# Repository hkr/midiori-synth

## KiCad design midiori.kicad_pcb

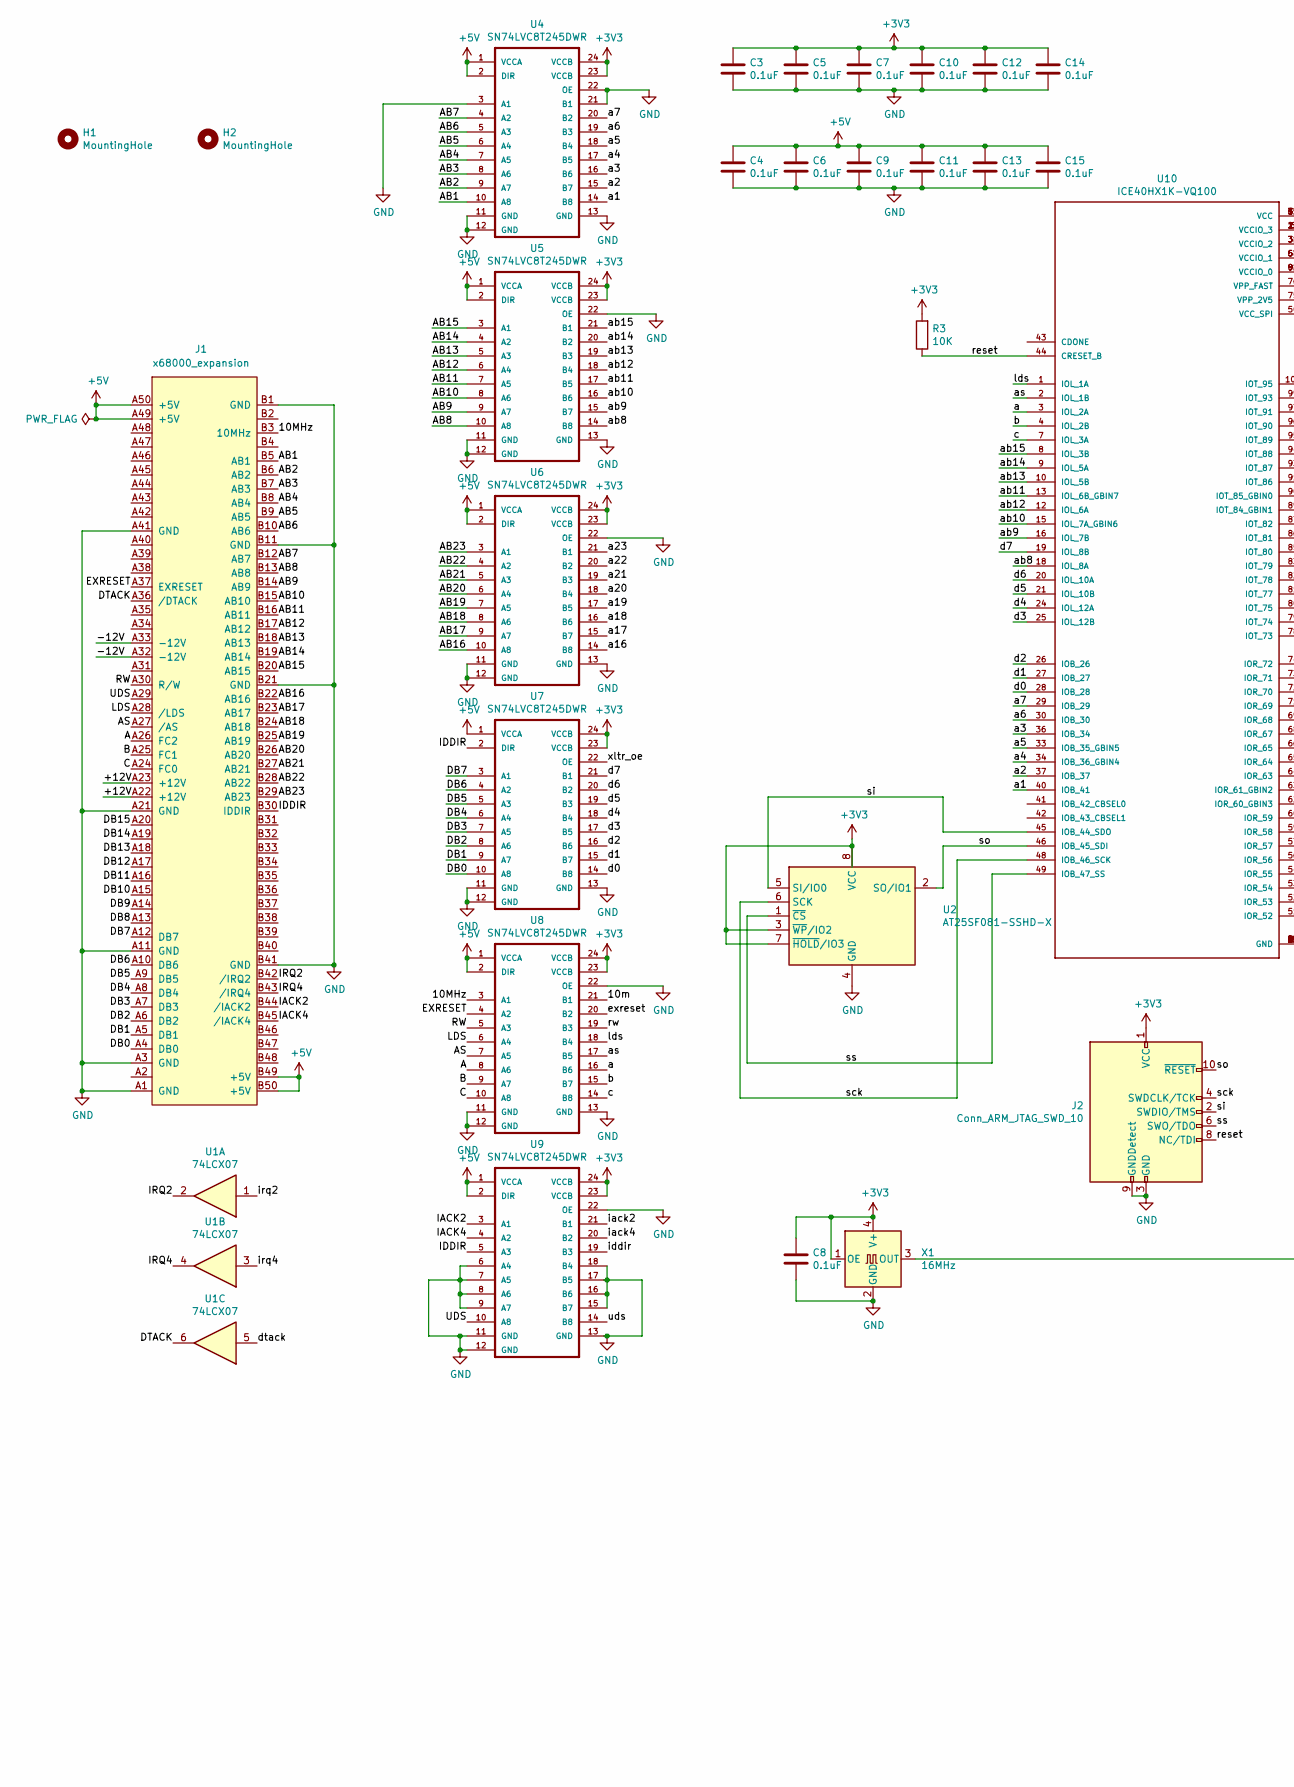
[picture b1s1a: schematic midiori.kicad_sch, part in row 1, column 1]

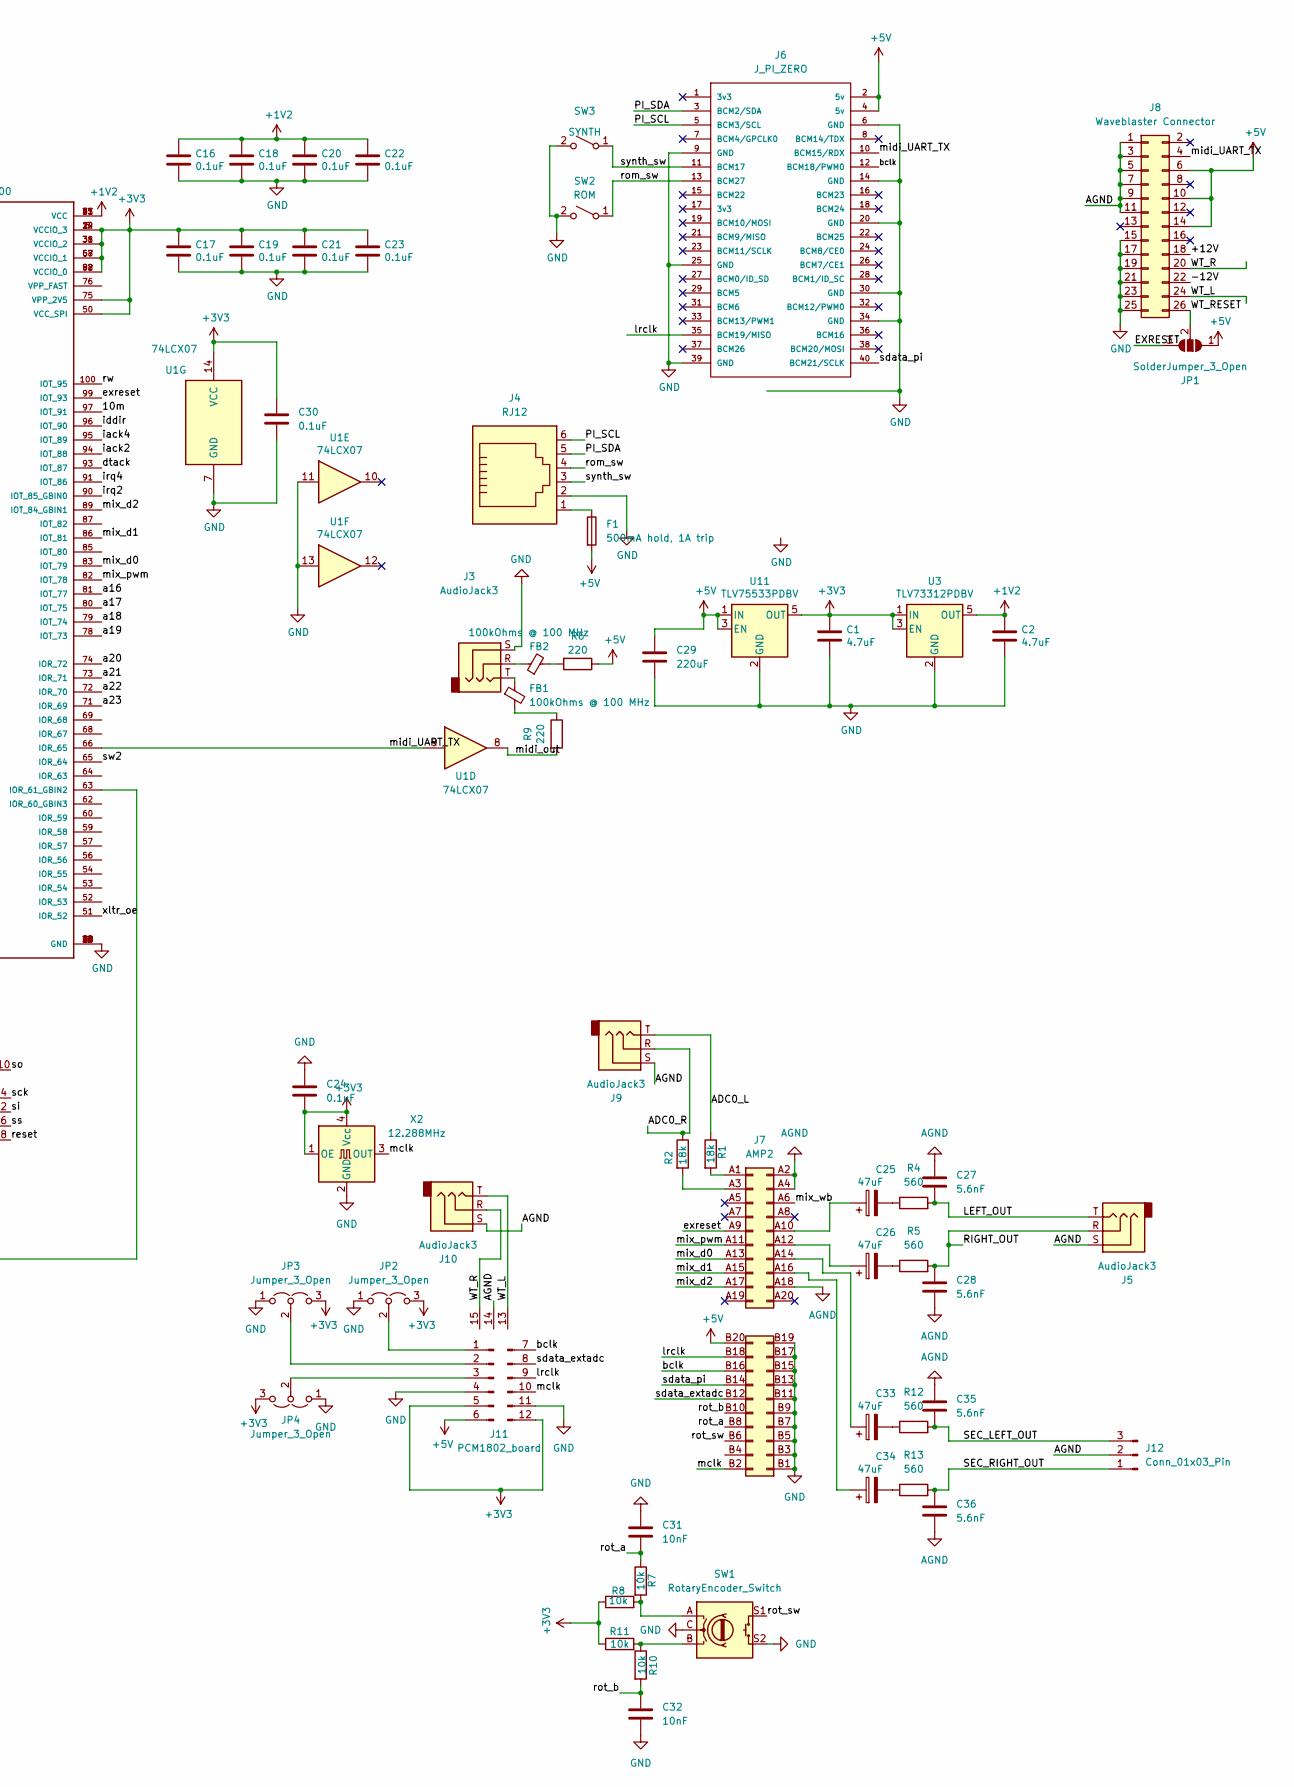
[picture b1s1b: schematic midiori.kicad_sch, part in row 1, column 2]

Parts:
C1, C2: 4.7uF; C_0805_2012Metric
C3, C4, C5, C6, C7, C9, C10, C11, C12, C13, C14, C15, C16, C17, C18, C19, C20, C21, C22, C23, C24, C30: 0.1uF; C_0805_2012Metric
C8: 0.1uF; C_0805_2012Metric_Pad1.15x1.40mm_HandSolder
C25, C26, C33, C34: 47uF; C_Elec_6.3x5.8
C27, C28, C35, C36: 5.6nF; C_0805_2012Metric
C29: 220uF; CP_Radial_D8.0mm_P3.50mm
C31, C32: 10nF; C_0805_2012Metric
F1: 500mA hold, 1A trip; Fuse_1206_3216Metric_Pad1.42x1.75mm_HandSolder
FB1, FB2: 100kOhms @ 100 MHz; L_0805_2012Metric_Pad1.05x1.20mm_HandSolder
H1, H2: MountingHole; MountingHole_3.2mm_M3_Pad
J1: x68000_expansion
J2: Conn_ARM_JTAG_SWD_10; PinHeader_2x05_P1.27mm_Vertical_SMD
J3, J5, J9, J10: AudioJack3; Jack_3.5mm_CUI_SJ1-3535NG_Horizontal
J4: RJ12; RJ12_Amphenol_54601-x06_Horizontal
J6: J_PI_ZERO; RASPBERRYPIZEROWV13
J7: AMP2; AMP2_TH
J8: Waveblaster Connector; PinHeader_2x13_P2.54mm_Vertical
J11: PCM1802_board; PCM1808_board
J12: Conn_01x03_Pin; PinHeader_1x03_P2.54mm_Horizontal
JP1: SolderJumper_3_Open; SolderJumper-3_P1.3mm_Open_Pad1.0x1.5mm
JP2, JP3, JP4: Jumper_3_Open; SolderJumper-3_P1.3mm_Open_RoundedPad1.0x1.5mm
R1, R2: 18k; R_0805_2012Metric
R3: 10K; R_0805_2012Metric
R4, R5, R12, R13: 560; R_0805_2012Metric
R6, R9: 220; R_0805_2012Metric_Pad1.15x1.40mm_HandSolder
R7, R8, R10, R11: 10k; R_0805_2012Metric
SW1: RotaryEncoder_Switch; RotaryEncoder_Bourns_Horizontal_PEC09-2xxxF-Sxxxx
SW2: ROM; SW_Tactile_SPST_Angled_PTS645Vx58-2LFS
SW3: SYNTH; SW_Tactile_SPST_Angled_PTS645Vx58-2LFS
U1: 74LCX07; SOIC-14_3.9x8.7mm_P1.27mm
U2: AT25SF081-SSHD-X; SOIC-8_3.9x4.9mm_P1.27mm
U3: TLV73312PDBV; SOT-23-5
U4, U5, U6, U7, U8, U9: SN74LVC8T245DWR; SOIC-24W_7.5x15.4mm_P1.27mm
U10: ICE40HX1K-VQ100; QFP50P1600X1600X120-100N
U11: TLV75533PDBV; SOT-23-5
X1: 16MHz; Oscillator_SMD_SeikoEpson_SG8002CA-4Pin_7.0x5.0mm
X2: 12.288MHz; Oscillator_SMD_SeikoEpson_SG8002CA-4Pin_7.0x5.0mm

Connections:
+1V2: C2.1, C16.1, C18.1, C20.1, C22.1, U3.5 (OUT), U10.11 (VCC), U10.35 (VCC), U10.61 (VCC), U10.77 (VCC)
+3V3: C1.1, C3.1, C5.1, C7.1, C8.1, C10.1, C12.1, C14.1, C17.1, C19.1, C21.1, C23.1, C24.2, C30.1, J2.1 (VCC), J11.5 (3V3), J11.12 (3V3), JP2.3 (B), JP3.3 (B), JP4.3 (B), R3.2, R8.1, R11.1, U1.14 (VCC), U2.3 (~WP/IO2), U2.7 (~HOLD/IO3), U2.8 (VCC), U3.1 (IN), U3.3 (EN), U4.23 (VCCB), U4.24 (VCCB), U5.23 (VCCB), U5.24 (VCCB), U6.23 (VCCB), U6.24 (VCCB), U7.23 (VCCB), U7.24 (VCCB), U8.23 (VCCB), U8.24 (VCCB), U9.23 (VCCB), U9.24 (VCCB), U10.6 (VCCIO_3), U10.14 (VCCIO_3), U10.22 (VCCIO_3), U10.31 (VCCIO_2), U10.38 (VCCIO_2), U10.50 (VCC_SPI), U10.58 (VCCIO_1), U10.67 (VCCIO_1), U10.75 (VPP_2V5), U10.88 (VCCIO_0), U10.92 (VCCIO_0), U11.5 (OUT), X1.1 (OE), X1.4 (V+), X2.1 (OE), X2.4 (Vcc)
+5V: C4.1, C6.1, C9.1, C11.1, C13.1, C15.1, C29.1, F1.2, J1.A49 (+5V), J1.A50 (+5V), J1.B49 (+5V), J1.B50 (+5V), J6.2 (5v), J6.4 (5v), J7.B20 (VIN), J8.6, J8.10, J8.14, J11.6 (5V), JP1.1 (A), R6.1, U4.1 (VCCA), U4.2 (DIR), U5.1 (VCCA), U5.2 (DIR), U6.1 (VCCA), U6.2 (DIR), U7.1 (VCCA), U8.1 (VCCA), U8.2 (DIR), U9.1 (VCCA), U9.2 (DIR), U11.1 (IN), U11.3 (EN)
/10MHz: J1.B3 (10MHz), U8.3 (A1)
/10m: U8.21 (B1), U10.97 (IOT_91)
/+12V: J1.A22 (+12V), J1.A23 (+12V), J8.18
/-12V: J1.A32 (-12V), J1.A33 (-12V), J8.22
/A: J1.A26 (FC2), U8.8 (A6)
/AB1: J1.B5 (AB1), U4.10 (A8)
/AB2: J1.B6 (AB2), U4.9 (A7)
/AB3: J1.B7 (AB3), U4.8 (A6)
/AB4: J1.B8 (AB4), U4.7 (A5)
/AB5: J1.B9 (AB5), U4.6 (A4)
/AB6: J1.B10 (AB6), U4.5 (A3)
/AB7: J1.B12 (AB7), U4.4 (A2)
/AB8: J1.B13 (AB8), U5.10 (A8)
/AB9: J1.B14 (AB9), U5.9 (A7)
/AB10: J1.B15 (AB10), U5.8 (A6)
/AB11: J1.B16 (AB11), U5.7 (A5)
/AB12: J1.B17 (AB12), U5.6 (A4)
/AB13: J1.B18 (AB13), U5.5 (A3)
/AB14: J1.B19 (AB14), U5.4 (A2)
/AB15: J1.B20 (AB15), U5.3 (A1)
/AB16: J1.B22 (AB16), U6.10 (A8)
/AB17: J1.B23 (AB17), U6.9 (A7)
/AB18: J1.B24 (AB18), U6.8 (A6)
/AB19: J1.B25 (AB19), U6.7 (A5)
/AB20: J1.B26 (AB20), U6.6 (A4)
/AB21: J1.B27 (AB21), U6.5 (A3)
/AB22: J1.B28 (AB22), U6.4 (A2)
/AB23: J1.B29 (AB23), U6.3 (A1)
/ADC0_L: J9.T, R1.1
/ADC0_R: J9.R, R2.1
/AS: J1.A27 (/AS), U8.7 (A5)
/B: J1.A25 (FC1), U8.9 (A7)
/C: J1.A24 (FC0), U8.10 (A8)
/DB0: J1.A4 (DB0), U7.10 (A8)
/DB1: J1.A5 (DB1), U7.9 (A7)
/DB2: J1.A6 (DB2), U7.8 (A6)
/DB3: J1.A7 (DB3), U7.7 (A5)
/DB4: J1.A8 (DB4), U7.6 (A4)
/DB5: J1.A9 (DB5), U7.5 (A3)
/DB6: J1.A10 (DB6), U7.4 (A2)
/DB7: J1.A12 (DB7), U7.3 (A1)
/DB8: J1.A13
/DB9: J1.A14
/DB10: J1.A15
/DB11: J1.A16
/DB12: J1.A17
/DB13: J1.A18
/DB14: J1.A19
/DB15: J1.A20
/DTACK: J1.A36 (/DTACK), U1.6
/EXRESET: J1.A37 (EXRESET), JP1.3 (B), U8.4 (A2)
/IACK2: J1.B44 (/IACK2), U9.3 (A1)
/IACK4: J1.B45 (/IACK4), U9.4 (A2)
/IDDIR: J1.B30 (IDDIR), U7.2 (DIR), U9.5 (A3)
/IRQ2: J1.B42 (/IRQ2), U1.2
/IRQ4: J1.B43 (/IRQ4), U1.4
/LDS: J1.A28 (/LDS), U8.6 (A4)
/LEFT_OUT: C27.2, J5.T, R4.2
/PI_SCL: J4.6, J6.5 (BCM3/SCL)
/PI_SDA: J4.5, J6.3 (BCM2/SDA)
/RIGHT_OUT: C28.1, J5.R, R5.2
/RW: J1.A30 (R/W), U8.5 (A3)
/SEC_LEFT_OUT: C35.2, J12.3, R12.2
/SEC_RIGHT_OUT: C36.1, J12.1, R13.2
/UDS: J1.A29, U9.10 (A8)
/WT_L: J8.24, J10.T, J11.13 (LIN)
/WT_R: J8.20, J10.R, J11.15 (RIN)
/WT_RESET: J8.26, JP1.2 (C)
/a: U8.16 (B6), U10.3 (IOL_2A)
/a1: U4.14 (B8), U10.40 (IOB_41)
/a2: U4.15 (B7), U10.37 (IOB_37)
/a3: U4.16 (B6), U10.36 (IOB_34)
/a4: U4.17 (B5), U10.34 (IOB_36_GBIN4)
/a5: U4.18 (B4), U10.33 (IOB_35_GBIN5)
/a6: U4.19 (B3), U10.30 (IOB_30)
/a7: U4.20 (B2), U10.29 (IOB_29)
/a16: U6.14 (B8), U10.81 (IOT_77)
/a17: U6.15 (B7), U10.80 (IOT_75)
/a18: U6.16 (B6), U10.79 (IOT_74)
/a19: U6.17 (B5), U10.78 (IOT_73)
/a20: U6.18 (B4), U10.74 (IOR_72)
/a21: U6.19 (B3), U10.73 (IOR_71)
/a22: U6.20 (B2), U10.72 (IOR_70)
/a23: U6.21 (B1), U10.71 (IOR_69)
/ab8: U5.14 (B8), U10.18 (IOL_8A)
/ab9: U5.15 (B7), U10.16 (IOL_7B)
/ab10: U5.16 (B6), U10.15 (IOL_7A_GBIN6)
/ab11: U5.17 (B5), U10.13 (IOL_6B_GBIN7)
/ab12: U5.18 (B4), U10.12 (IOL_6A)
/ab13: U5.19 (B3), U10.10 (IOL_5B)
/ab14: U5.20 (B2), U10.9 (IOL_5A)
/ab15: U5.21 (B1), U10.8 (IOL_3B)
/as: U8.17 (B5), U10.2 (IOL_1B)
/b: U8.15 (B7), U10.4 (IOL_2B)
/bclk: J6.12 (BCM18/PWM0), J7.B16 (MP5), J11.7 (BCK)
/c: U8.14 (B8), U10.7 (IOL_3A)
/d0: U7.14 (B8), U10.28 (IOB_28)
/d1: U7.15 (B7), U10.27 (IOB_27)
/d2: U7.16 (B6), U10.26 (IOB_26)
/d3: U7.17 (B5), U10.25 (IOL_12B)
/d4: U7.18 (B4), U10.24 (IOL_12A)
/d5: U7.19 (B3), U10.21 (IOL_10B)
/d6: U7.20 (B2), U10.20 (IOL_10A)
/d7: U7.21 (B1), U10.19 (IOL_8B)
/dtack: U1.5, U10.93 (IOT_87)
/exreset: J7.A9 (/RESET), U8.20 (B2), U10.99 (IOT_93)
/iack2: U9.21 (B1), U10.94 (IOT_88)
/iack4: U9.20 (B2), U10.95 (IOT_89)
/iddir: U9.19 (B3), U10.96 (IOT_90)
/irq2: U1.1, U10.90 (IOT_85_GBIN0)
/irq4: U1.3, U10.91 (IOT_86)
/lds: U8.18 (B4), U10.1 (IOL_1A)
/lrclk: J6.35 (BCM19/MISO), J7.B18 (MP4), J11.9 (LRC)
/mclk: J7.B2 (MCLK), J11.10 (SCK), X2.3 (OUT)
/midi_UART_TX: J6.10 (BCM15/RDX), J8.4, U1.9, U10.66 (IOR_65)
/midi_out: R9.2, U1.8
/mix_d0: J7.A13 (MP3), U10.83 (IOT_79)
/mix_d1: J7.A15 (MP8), U10.86 (IOT_81)
/mix_d2: J7.A17 (MP9), U10.89 (IOT_84_GBIN1)
/mix_pwm: J7.A11 (MP2), U10.82 (IOT_78)
/mix_wb: J7.A6 (WB)
/reset: J2.8 (NC/TDI), R3.1, U10.44 (CRESET_B)
/rom_sw: J4.4, J6.13 (BCM27), SW2.1 (A)
/rot_a: C31.2, J7.B8 (MP6), R7.1
/rot_b: C32.2, J7.B10 (MP7), R10.2
/rot_sw: J7.B6 (MP10), SW1.S1
/rw: U8.19 (B3), U10.100 (IOT_95)
/sck: J2.4 (SWDCLK/TCK), U2.6 (SCK), U10.48 (IOB_46_SCK)
/sdata_extadc: J7.B12 (MP0), J11.8 (OUT)
/sdata_pi: J6.40 (BCM21/SCLK), J7.B14 (MP1)
/si: J2.2 (SWDIO/TMS), U2.5 (SI/IO0), U10.45 (IOB_44_SDO)
/so: J2.10 (~RESET), U2.2 (SO/IO1), U10.46 (IOB_45_SDI)
/ss: J2.6 (SWO/TDO), U2.1 (~CS), U10.49 (IOB_47_SS)
/sw2: U10.65 (IOR_64)
/synth_sw: J4.3, J6.11 (BCM17), SW3.1 (A)
/uds: U9.14 (B8)
/xltr_oe: U7.22 (OE), U10.51 (IOR_52)
AGND: C27.1, C28.2, C35.1, C36.2, J5.S, J7.A2 (GND), J7.A4 (GND), J7.A18 (GND), J8.1, J8.3, J8.5, J8.7, J8.9, J8.11, J9.S, J10.S, J11.14 (GND), J12.2
GND: C1.2, C2.2, C3.2, C4.2, C5.2, C6.2, C7.2, C8.2, C9.2, C10.2, C11.2, C12.2, C13.2, C14.2, C15.2, C16.2, C17.2, C18.2, C19.2, C20.2, C21.2, C22.2, C23.2, C24.1, C29.2, C30.2, C31.1, C32.1, J1.A1 (GND), J1.A3 (GND), J1.A11 (GND), J1.A21 (GND), J1.A41 (GND), J1.B1 (GND), J1.B11 (GND), J1.B21 (GND), J1.B41 (GND), J2.3 (GND), J2.5 (GND), J2.9 (GNDDetect), J3.S, J4.2, J6.6 (GND), J6.9 (GND), J6.14 (GND), J6.20 (GND), J6.25 (GND), J6.30 (GND), J6.34 (GND), J6.39 (GND), J7.B1 (GND), J7.B3 (GND), J7.B5 (GND), J7.B7 (GND), J7.B9 (GND), J7.B11 (GND), J7.B13 (GND), J7.B15 (GND), J7.B17 (GND), J7.B19 (GND), J8.15, J8.17, J8.19, J8.21, J8.23, J8.25, J11.4 (GND), J11.11 (GND), JP2.1 (A), JP3.1 (A), JP4.1 (A), SW1.C, SW1.S2, SW2.2 (B), SW3.2 (B), U1.7 (GND), U1.11, U1.13, U2.4 (GND), U3.2 (GND), U4.3 (A1), U4.11 (GND), U4.12 (GND), U4.13 (GND), U4.21 (B1), U4.22 (OE), U5.11 (GND), U5.12 (GND), U5.13 (GND), U5.22 (OE), U6.11 (GND), U6.12 (GND), U6.13 (GND), U6.22 (OE), U7.11 (GND), U7.12 (GND), U7.13 (GND), U8.11 (GND), U8.12 (GND), U8.13 (GND), U8.22 (OE), U9.6 (A4), U9.7 (A5), U9.8 (A6), U9.9 (A7), U9.11 (GND), U9.12 (GND), U9.13 (GND), U9.15 (B7), U9.16 (B6), U9.17 (B5), U9.18 (B4), U9.22 (OE), U10.5 (GND), U10.17 (GND), U10.23 (GND), U10.32 (GND), U10.39 (GND), U10.47 (GND), U10.55 (GND), U10.70 (GND), U10.84 (GND), U10.98 (GND), U11.2 (GND), X1.2 (GND), X2.2 (GND)
unnamed: C25.2, R4.1
unnamed: C26.2, R5.1
unnamed: C33.2, R12.1
unnamed: C34.2, R13.1
unnamed: F1.1, J4.1
unnamed: FB1.1, J3.T
unnamed: FB1.2, R9.1
unnamed: FB2.1, J3.R
unnamed: FB2.2, R6.2
unnamed: J7.A1 (AD0), R1.2
unnamed: J7.A3 (AD1), R2.2
unnamed: C25.1, J7.A10 (DAC0)
unnamed: C26.1, J7.A12 (DAC1)
unnamed: C33.1, J7.A14 (DAC2)
unnamed: C34.1, J7.A16 (DAC3)
unnamed: J11.3 (MD0), JP4.2 (C)
unnamed: J11.2 (MD1), JP3.2 (C)
unnamed: J11.1, JP2.2 (C)
unnamed: R7.2, R8.2, SW1.A
unnamed: R10.1, R11.2, SW1.B
unnamed: U10.63 (IOR_61_GBIN2), X1.3 (OUT)

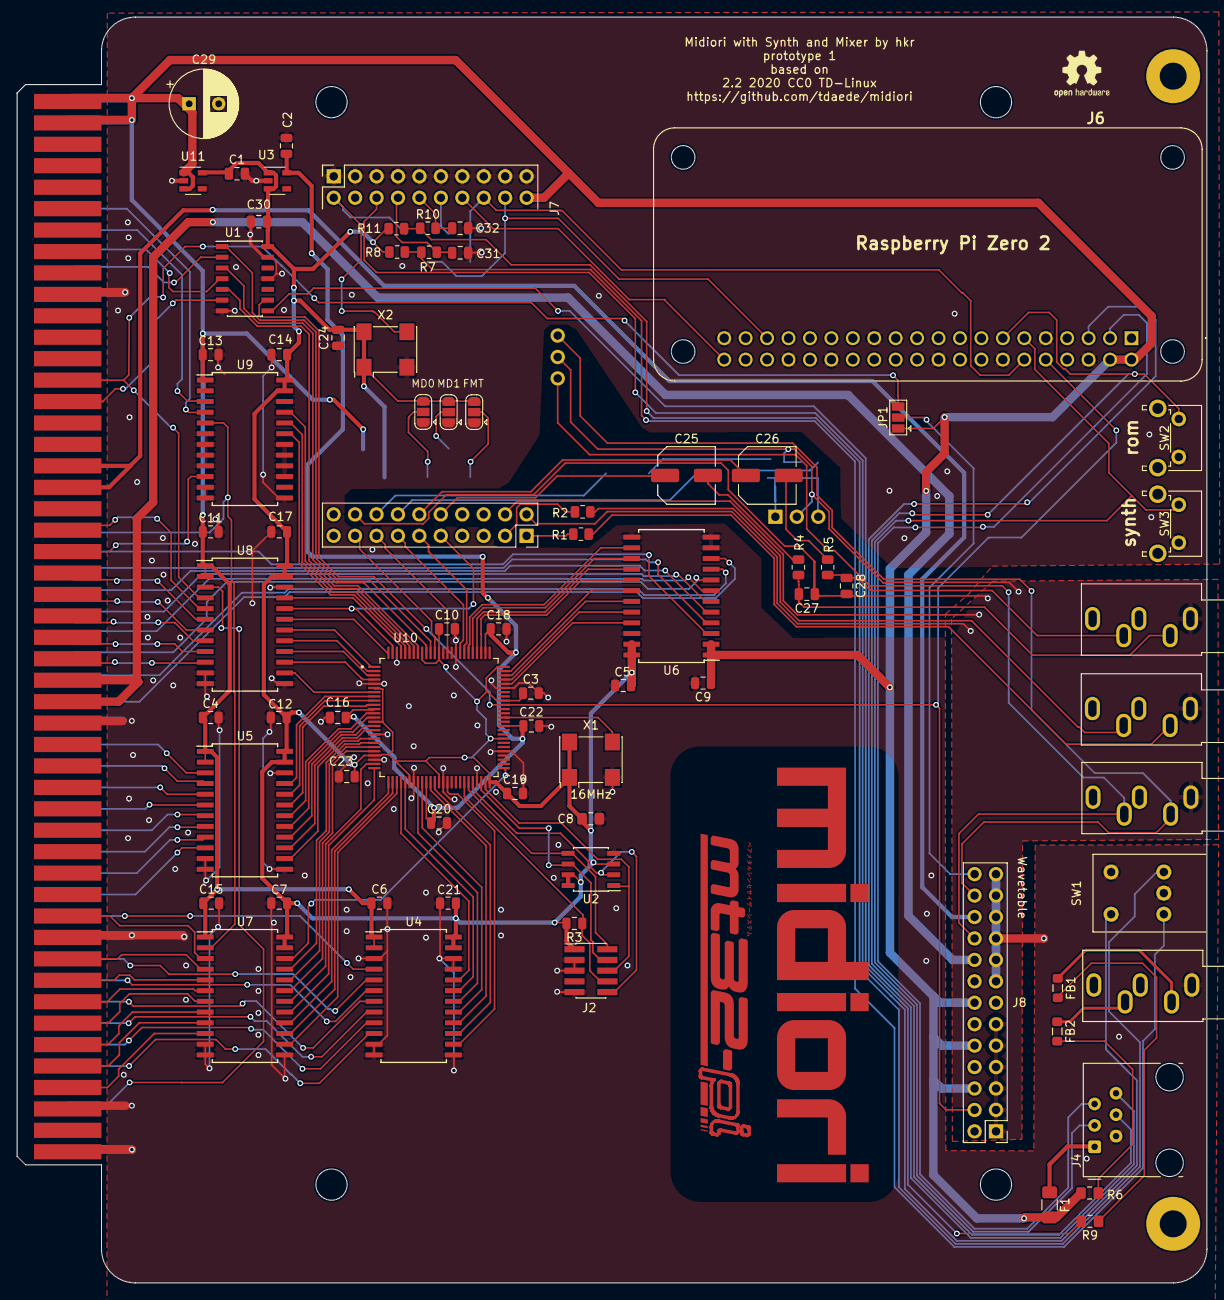
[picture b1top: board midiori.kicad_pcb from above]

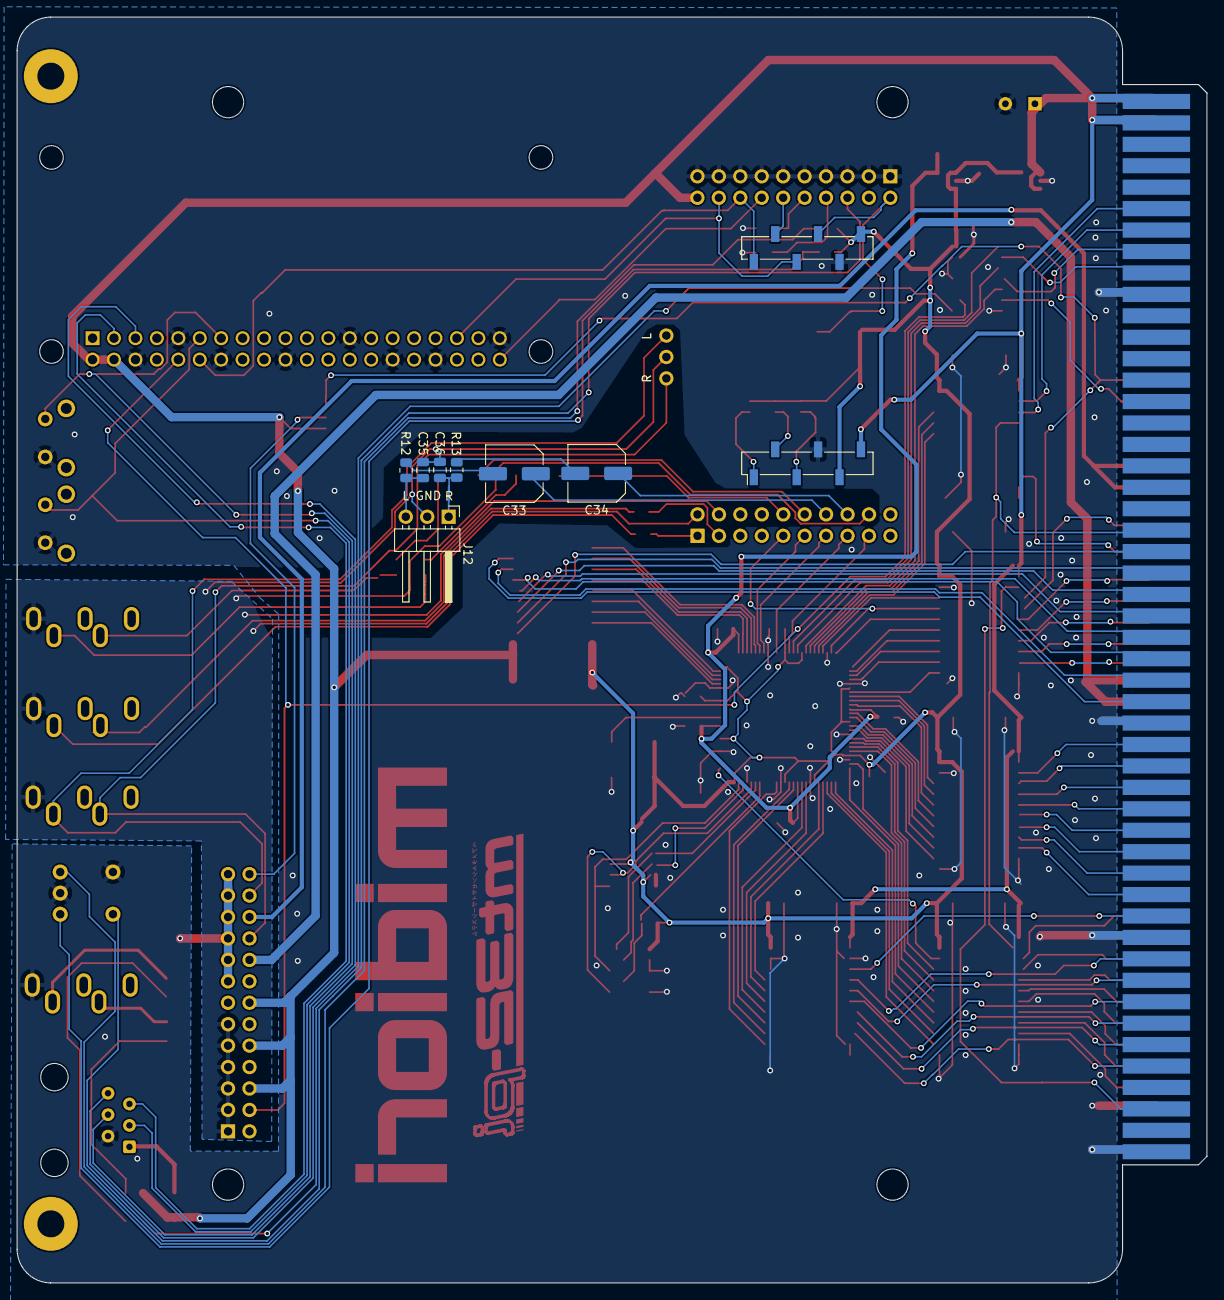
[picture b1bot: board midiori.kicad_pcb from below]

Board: 2 copper layers, 141.0 x 150.0 mm, 87 parts (8 on the bottom side), 152 nets.

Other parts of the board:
svg2mod: G***; midiori_logo

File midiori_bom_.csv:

Component,Description,Part,References,Value,Footprint,Quantity Per PCB,Datasheet,Field4,Field5,Field6,Field7,Field8
1,Unpolarized capacitor,C,C3 C4 C5 C6 C7 C9 C10 C11 C12 C13 C14 C15 C16 C17 C18 C19 C20 C21 C22 C23 C28 C30,0.1uF,C_0805_2012Metric,22,~,,,,,
2,Unpolarized capacitor,C,C8,0.1uF,C_0805_2012Metric_Pad1.15x1.40mm_HandSolder,1,~,,,,,
3,Unpolarized capacitor,C,C1 C2,4.7uF,C_0805_2012Metric,2,~,,,,,
4,Unpolarized capacitor,C,C29,220uF,CP_Radial_D8.0mm_P3.50mm,1,~,,,,,
5,Fuse,Fuse,F1,"500mA hold, 1A trip",Fuse_1206_3216Metric_Pad1.42x1.75mm_HandSolder,1,~,,,,,
6,"Ferrite bead, small symbol",FerriteBead_Small,FB1 FB2,100kOhms @ 100 MHz,L_0805_2012Metric_Pad1.05x1.20mm_HandSolder,2,~,,,,,
7,"Audio Jack, 3 Poles (Stereo / TRS)",AudioJack3,J3,AudioJack3,Jack_3.5mm_CUI_SJ1-3535NG_Horizontal,1,~,,,,,
8,"Audio Jack, 3 Poles (Stereo / TRS)",AudioJack3,J5 J9,AudioJack3,Jack_3.5mm_CUI_SJ1-3535NG_Horizontal,2,~,,,,,
9,,Conn_ARM_JTAG_SWD_10-Connector-midiori-rescue-midiori-rescue,J2,Conn_ARM_JTAG_SWD_10,PinHeader_2x05_P1.27mm_Vertical_SMD,1,http://infocenter.arm.com/help/topic/com.arm.doc.faqs/attach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,,,,,
10,,J_PI_ZERO,J6,J_PI_ZERO,RASPBERRYPIZEROWV13,1,,,,,,
11,"RJ connector, 6P6C (6 positions 6 connected)",RJ12,J4,RJ12,RJ12_Amphenol_54601-x06_Horizontal,1,~,,,,,
12,"Generic connector, double row, 02x13, odd/even pin numbering scheme (row 1 odd numbers, row 2 even numbers), script generated (kicad-library-utils/schlib/autogen/connector/)",Conn_02x13_Odd_Even,J8,Waveblaster Connector,PinHeader_2x13_P2.54mm_Vertical,1,~,,,,,
13,,x68000_expansion-x68k-midiori-rescue-midiori-rescue,J1,x68000_expansion,x68000_expansion,1,,,,,,
14,"Solder Jumper, 3-pole, open",SolderJumper_3_Open,JP1,SolderJumper_3_Open,SolderJumper-3_P1.3mm_Open_Pad1.0x1.5mm,1,~,,,,,
15,Resistor,R,R6 R9,220,R_0805_2012Metric_Pad1.15x1.40mm_HandSolder,2,~,,,,,
16,Resistor,R,R3,10K,R_0805_2012Metric,1,~,,,,,
17,Resistor,R,R4 R5 R7 R8 R10 R11,47k,R_0805_2012Metric_Pad1.20x1.40mm_HandSolder,6,~,,,,,
18,Single Pole Single Throw (SPST) switch,SW_SPST,SW2,ROM,SW_Tactile_SPST_Angled_PTS645Vx58-2LFS,1,~,,,,,
19,,SS-10-23NPE,SW4,SS-10-23NPE,SS1023NPE,1,SS-10-23NPE,,,,,
20,Single Pole Single Throw (SPST) switch,SW_SPST,SW3,SYNTH,SW_Tactile_SPST_Angled_PTS645Vx58-2LFS,1,~,,,,,
21,CMOS hex buffer (open drain) with 5V tolerant inputs,74LCX07,U1,74LCX07,SOIC-14_3.9x8.7mm_P1.27mm,1,www.st.com/resource/en/datasheet/74lcx07.pdf,,,,,
22,"8-Mbit, 2.5V Minimum SPI Serial Flash Memory with Dual-I/O and Quad-I/O Support, SOIC-8",AT25SF081-SSHD-X,U2,AT25SF081-SSHD-X,SOIC-8_3.9x4.9mm_P1.27mm,1,https://www.adestotech.com/wp-content/uploads/DS-AT25SF081_045.pdf,,,,,
23,,ICE40HX1K-VQ100-ICE40HX1K-VQ100-midiori-rescue-midiori-rescue,U10,ICE40HX1K-VQ100,QFP50P1600X1600X120-100N,1,Lattice Semiconductor,Warning,HX Series 1280 LUTs 95 I/O 64 kBit RAM 1.2 V Surface Mount FPGA - VQFP-100,3.77 USD,TQFP-100 Lattice Semiconductor,ICE40HX1K-VQ100
24,,SN74LVC8T245DWR-SN74LVC8T245DWR-midiori-rescue-midiori-rescue,U4 U5 U6 U7 U8 U9,SN74LVC8T245DWR,SOIC-24W_7.5x15.4mm_P1.27mm,6,SOIC-24 Texas Instruments,Texas Instruments,Good,0.61 USD,SN74LVC8T245DWR,8-Bit Dual-Supply Bus Transceiver with Configurable Voltage Translation and Three-State Outputs 24-SOIC -40 to 85
25,"300mA Capacitor-Free Low Dropout Voltage Regulator, Fixed Output 1.2V, SOT-23-5",TLV73312PDBV,U3,TLV73312PDBV,SOT-23-5,1,http://www.ti.com/lit/ds/symlink/tlv733p.pdf,,,,,
26,"300mA Capacitor-Free Low Dropout Voltage Regulator, Fixed Output 3.3V, SOT-23-5",TLV73333PDBV,U11,TLV75533PDBV,SOT-23-5,1,http://www.ti.com/lit/ds/symlink/tlv733p.pdf,,,,,
27,,U_GY-PCM5102,U15,U_GY-PCM5102,U_GY-PCM5102,1,,,,,,
28,,SG5032CAN-x68k-midiori-rescue-midiori-rescue,X1,16MHz,Oscillator_SMD_SeikoEpson_SG8002CA-4Pin_7.0x5.0mm,1,http://cdn-reichelt.de/documents/datenblatt/B400/OSZI.pdf,,,,,





Component Groups:,28
Component Count:,63
Fitted Components:,63
Number of PCBs:,1
Total components:,63
Schematic Version:,
Schematic Date:,
PCB Variant:,default
BoM Date:,"Saturday, February 24, 2024 at 03:55:45 PM"
Schematic Source:,midiori.kicad_sch
KiCad Version:,Eeschema 7.0.10

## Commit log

2024-02-25 Added synth addon
2024-02-25 Fixed some traces
2024-02-25 Remove unused files
2024-02-25 Update license
2025-02-15 Development board

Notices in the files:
midiori.kicad_pcb:
2.2 2020 CC0 TD-Linux
